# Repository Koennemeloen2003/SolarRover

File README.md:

Code en PSB design voor het Solar Rover project van hogeschool Zuyd

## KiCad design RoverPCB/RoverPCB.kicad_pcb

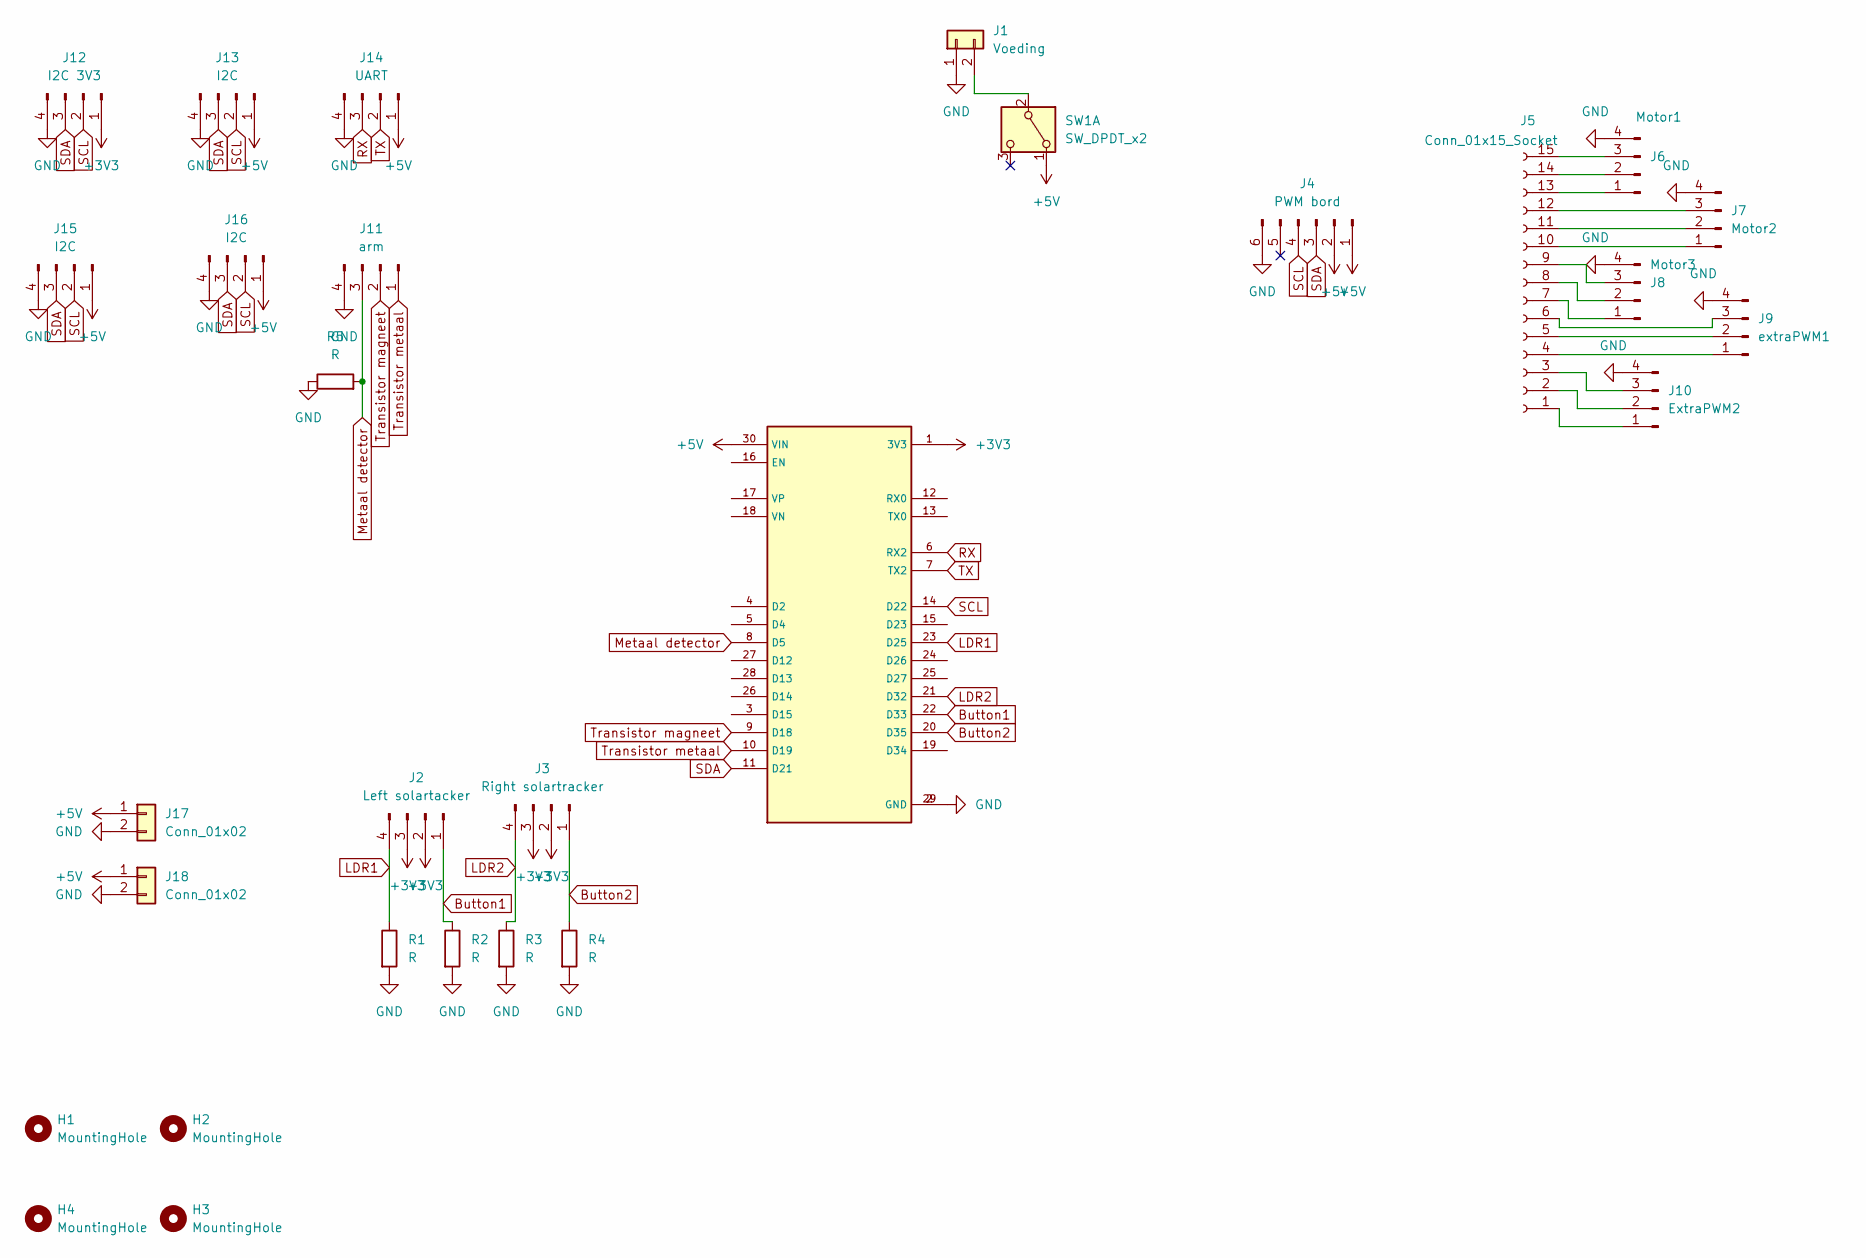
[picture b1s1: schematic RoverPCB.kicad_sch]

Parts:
H1, H2, H3, H4: MountingHole; MountingHole_3.2mm_M3
J1: Voeding; PhoenixContact_MSTBA_2,5_2-G-5,08_1x02_P5.08mm_Horizontal
J2: Left solartacker; Audio jack
J3: Right solartracker; Audio jack
J4: PWM bord; PinHeader_1x06_P2.54mm_Vertical
J5: Conn_01x15_Socket; PinHeader_1x15_P2.54mm_Vertical
J6: Motor1; Audio jack
J7: Motor2; Audio jack
J8: Motor3; Audio jack
J9: extraPWM1; Audio jack
J10: ExtraPWM2; Audio jack
J11: arm; Audio jack
J12: I2C 3V3; Audio jack
J13, J15, J16: I2C; Audio jack
J14: UART; Audio jack
J17, J18: Conn_01x02; PinHeader_1x02_P2.54mm_Vertical
R1, R2, R3, R4, R5: R; R_Axial_DIN0204_L3.6mm_D1.6mm_P7.62mm_Horizontal
SW1: SW_DPDT_x2; SW_CuK_SPDT_Angled
U1: ESP32_DEVKIT_V1_op_voetjes2rij

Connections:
+3V3: J2.2, J2.3, J3.2, J3.3, J12.1, U1.1 (3V3)
+5V: J4.1, J4.2, J13.1, J14.1, J15.1, J16.1, J17.1, J18.1, SW1.1 (A), U1.30 (VIN)
Button1: J2.1, R2.1, U1.22 (D33)
Button2: J3.1, R4.1, U1.20 (D35)
GND: J1.1, J4.6, J6.4, J7.4, J8.4, J9.4, J10.4, J11.4, J12.4, J13.4, J14.4, J15.4, J16.4, J17.2, J18.2, R1.2, R2.2, R3.2, R4.2, R5.1, U1.2 (GND), U1.29 (GND)
LDR1: J2.4, R1.1, U1.23 (D25)
LDR2: J3.4, R3.1, U1.21 (D32)
Metaal detector: J11.3, R5.2, U1.8 (D5)
unnamed: J1.2, SW1.2 (B)
unnamed: J5.4, J9.1
unnamed: J5.5, J9.2
unnamed: J5.6, J9.3
unnamed: J5.7, J8.1
unnamed: J5.8, J8.2
unnamed: J5.9, J8.3
unnamed: J5.10, J7.1
unnamed: J5.11, J7.2
unnamed: J5.12, J7.3
unnamed: J5.13, J6.1
unnamed: J5.14, J6.2
unnamed: J5.15, J6.3
unnamed: J5.1, J10.1
unnamed: J5.2, J10.2
unnamed: J5.3, J10.3
RX: J14.3, U1.6 (RX2)
SCL: J4.4, J12.2, J13.2, J15.2, J16.2, U1.14 (D22)
SDA: J4.3, J12.3, J13.3, J15.3, J16.3, U1.11 (D21)
TX: J14.2, U1.7 (TX2)
Transistor magneet: J11.2, U1.9 (D18)
Transistor metaal: J11.1, U1.10 (D19)

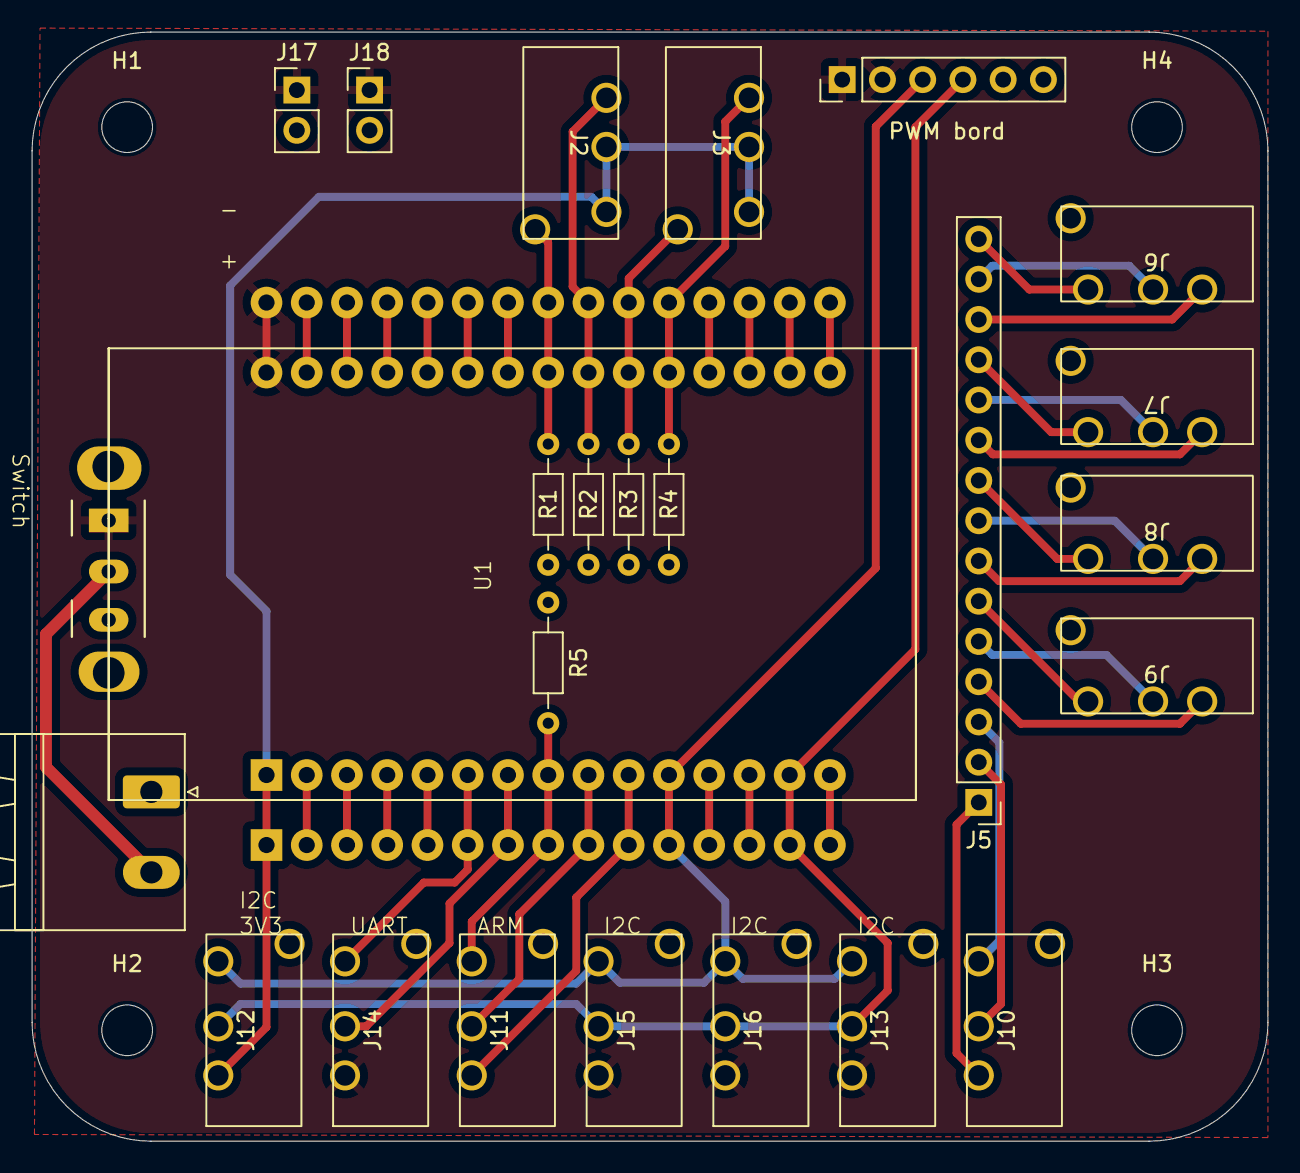
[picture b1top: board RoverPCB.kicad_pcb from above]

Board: 2 copper layers, 78.0 x 70.0 mm, 29 parts (0 on the bottom side), 30 nets.

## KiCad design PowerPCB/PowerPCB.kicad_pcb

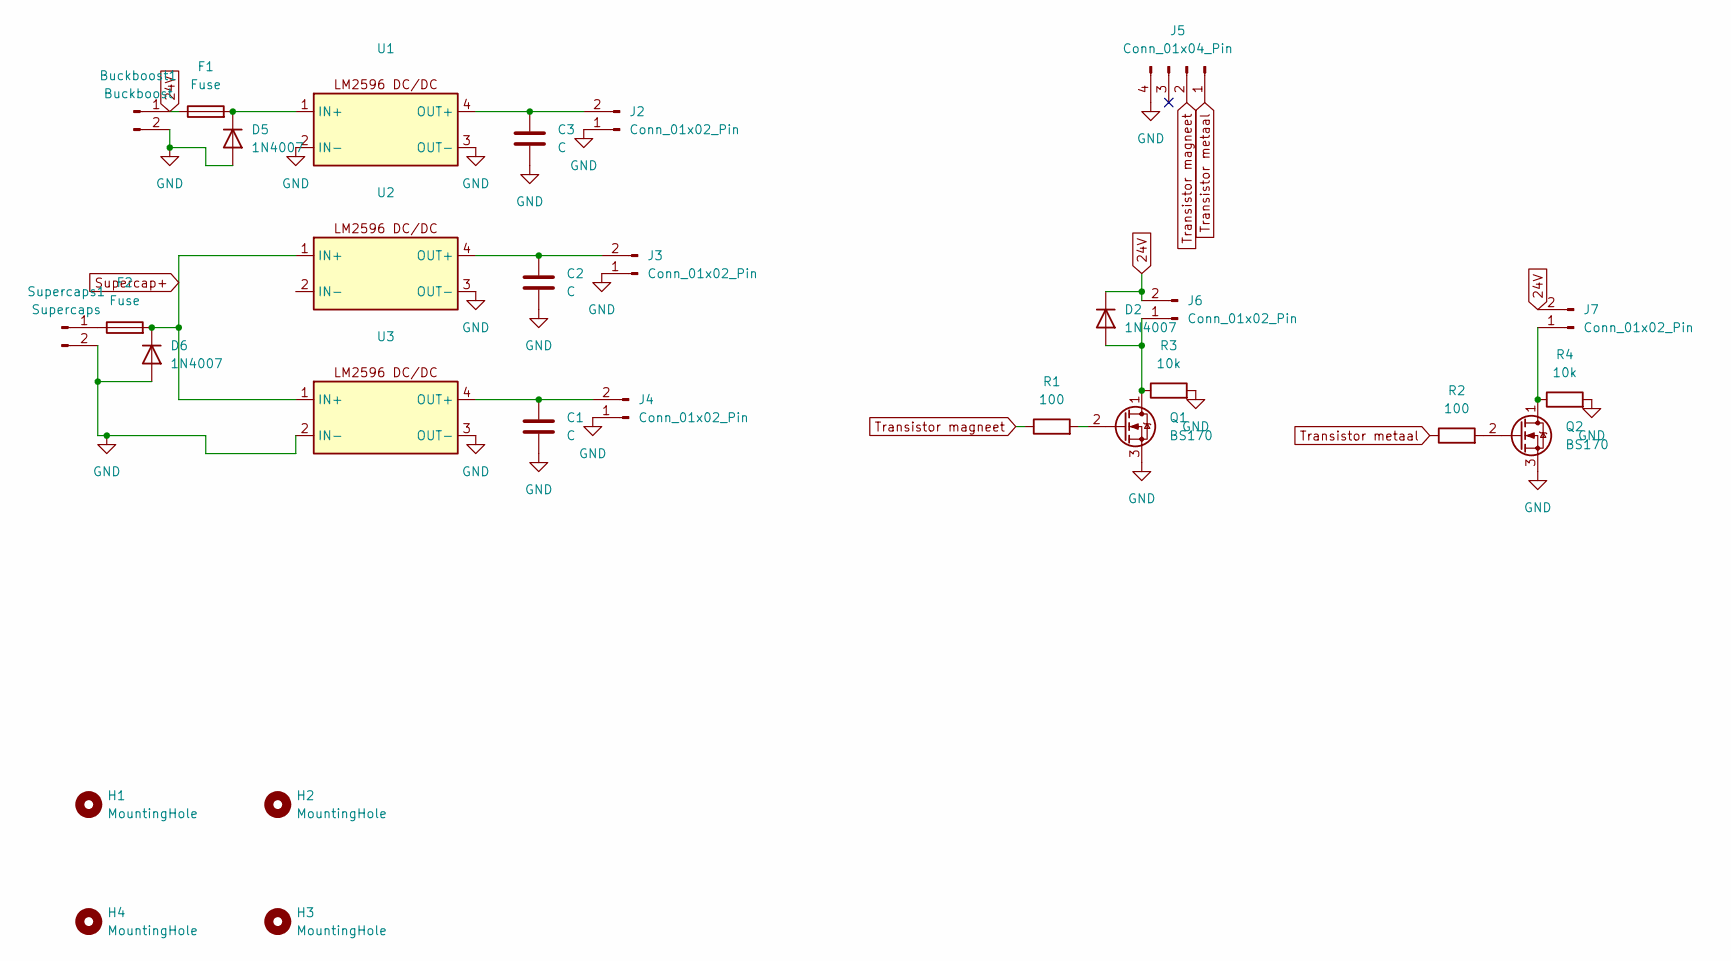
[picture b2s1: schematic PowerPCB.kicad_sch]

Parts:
Buckboost1: Buckboost; PhoenixContact_MSTBA_2,5_2-G-5,08_1x02_P5.08mm_Horizontal
C1, C2, C3: C; CP_Radial_D5.0mm_P2.50mm
D2, D5, D6: 1N4007; D_DO-41_SOD81_P10.16mm_Horizontal
F1, F2: Fuse; RB500-50
H1, H2, H3, H4: MountingHole; MountingHole_3.2mm_M3
J2, J3, J4, J6, J7: Conn_01x02_Pin; PhoenixContact_MSTBA_2,5_2-G-5,08_1x02_P5.08mm_Horizontal
J5: Conn_01x04_Pin; Audio jack
Q1, Q2: BS170; TO-92_Inline
R1, R2: 100; R_Axial_DIN0204_L3.6mm_D1.6mm_P7.62mm_Horizontal
R3, R4: 10k; R_Axial_DIN0204_L3.6mm_D1.6mm_P7.62mm_Horizontal
Supercaps1: Supercaps; PhoenixContact_MSTBA_2,5_2-G-5,08_1x02_P5.08mm_Horizontal
U1, U2, U3: LM2596_module_opvoetjes

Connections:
24V: Buckboost1.1, D2.1 (K), F1.1, J6.2, J7.2
GND: Buckboost1.2, C1.2, C2.2, C3.2, D5.2 (A), D6.2 (A), J2.1, J3.1, J4.1, J5.4, Q1.3 (S), Q2.3 (S), R3.2, R4.2, Supercaps1.2, U1.2 (IN-), U1.3 (OUT-), U2.3 (OUT-), U3.2 (IN-), U3.3 (OUT-)
unnamed: D2.2 (A), J6.1, Q1.1 (D), R3.1
unnamed: D5.1 (K), F1.2, U1.1 (IN+)
unnamed: C3.1, J2.2, U1.4 (OUT+)
unnamed: C2.1, J3.2, U2.4 (OUT+)
unnamed: C1.1, J4.2, U3.4 (OUT+)
unnamed: J7.1, Q2.1 (D), R4.1
unnamed: Q1.2 (G), R1.2
unnamed: Q2.2 (G), R2.2
unnamed: F2.1, Supercaps1.1
Supercap+: D6.1 (K), F2.2, U2.1 (IN+), U3.1 (IN+)
Transistor magneet: J5.2, R1.1
Transistor metaal: J5.1, R2.1

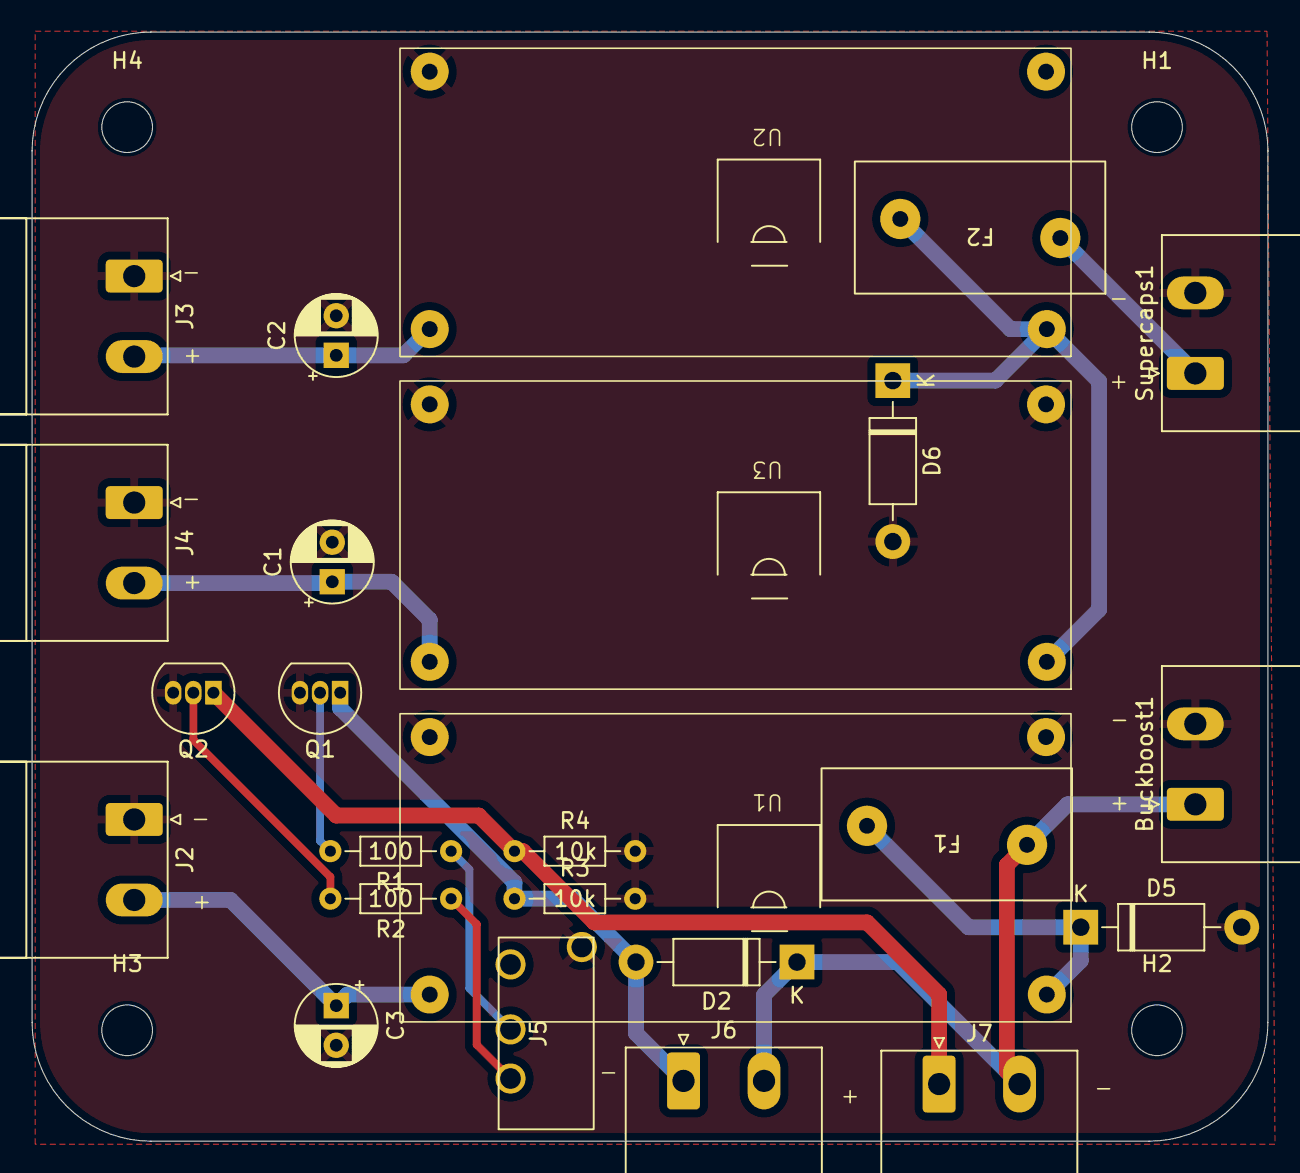
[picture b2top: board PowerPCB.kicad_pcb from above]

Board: 2 copper layers, 78.0 x 70.0 mm, 29 parts (0 on the bottom side), 14 nets.

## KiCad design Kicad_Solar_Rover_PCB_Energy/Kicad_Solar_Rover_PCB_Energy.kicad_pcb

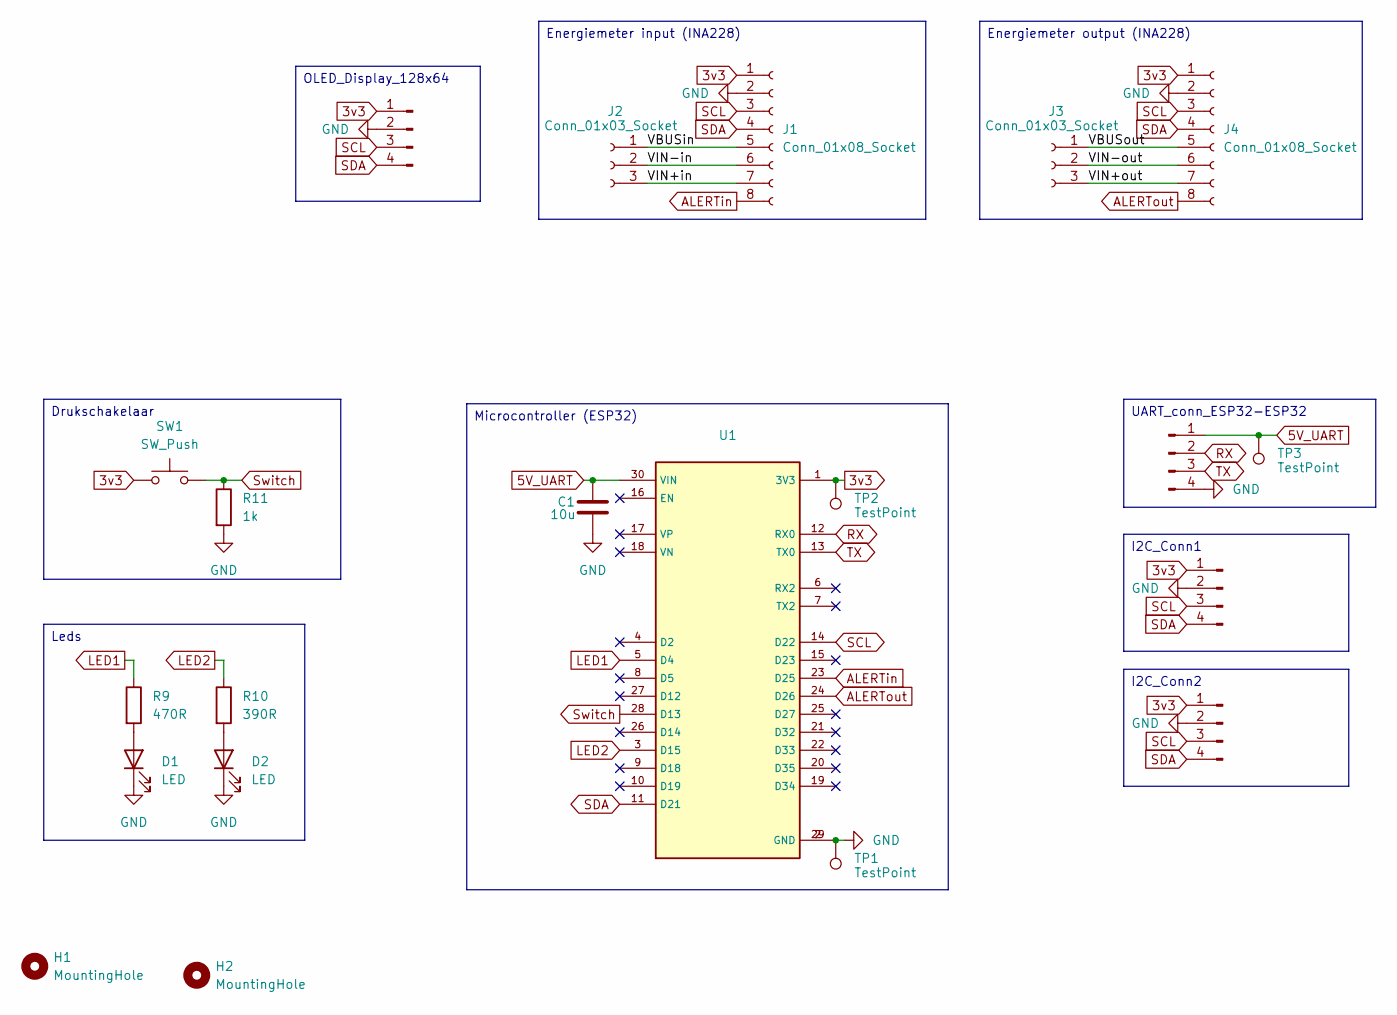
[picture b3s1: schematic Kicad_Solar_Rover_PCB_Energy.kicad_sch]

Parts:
C1: 10u; CP_Axial_L10.0mm_D4.5mm_P15.00mm_Horizontal
D1, D2: LED; LED_D5.0mm; MPN LWTTM1P1FK0PN005
H1, H2: MountingHole; MountingHole_4.3mm_M4
J1, J4: Conn_01x08_Socket; PinSocket_1x08_P2.54mm_Vertical
J2, J3: Conn_01x03_Socket; PhoenixContact_MSTBA_2,5_3-G-5,08_1x03_P5.08mm_Horizontal
J5, J7, J8, J9: Conn_01x04_Pin; Audio jack; MPN 9-103329-0
R9: 470R; R_Axial_DIN0207_L6.3mm_D2.5mm_P7.62mm_Horizontal; MPN CRCW0603-1.3K-E3
R10: 390R; R_Axial_DIN0207_L6.3mm_D2.5mm_P7.62mm_Horizontal; MPN CRCW0603-1.3K-E3
R11: 1k; R_Axial_DIN0207_L6.3mm_D2.5mm_P7.62mm_Horizontal; MPN CRCW06031K00FKEI
SW1: SW_Push; SW_PUSH_6mm_H8mm; MPN KMR231GLFS
TP1, TP2, TP3: TestPoint; TestPoint_Pad_D1.0mm
U1: ESP32_DEVKIT_V1

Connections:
3v3: J1.1, J4.1, J7.1, J8.1, J9.1, SW1.1, TP2.1, U1.1 (3V3)
5V_UART: C1.1, J5.1, TP3.1, U1.30 (VIN)
/VBUSin: J1.5, J2.1
/VBUSout: J3.1, J4.5
/VIN+in: J1.7, J2.3
/VIN+out: J3.3, J4.7
/VIN-in: J1.6, J2.2
/VIN-out: J3.2, J4.6
ALERTin: J1.8, U1.23 (D25)
ALERTout: J4.8, U1.24 (D26)
GND: C1.2, D1.1 (K), D2.1 (K), J1.2, J4.2, J5.4, J7.2, J8.2, J9.2, R11.2, TP1.1, U1.2 (GND), U1.29 (GND)
LED1: R9.1, U1.5 (D4)
LED2: R10.1, U1.3 (D15)
unnamed: D1.2 (A), R9.2
unnamed: D2.2 (A), R10.2
RX: J5.2, U1.12 (RX0)
SCL: J1.3, J4.3, J7.3, J8.3, J9.3, U1.14 (D22)
SDA: J1.4, J4.4, J7.4, J8.4, J9.4, U1.11 (D21)
Switch: R11.1, SW1.2, U1.28 (D13)
TX: J5.3, U1.13 (TX0)

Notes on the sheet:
I2C_Conn1
Leds
Microcontroller (ESP32)
Energiemeter input (INA228)
I2C_Conn2
UART_conn_ESP32-ESP32
OLED_Display_128x64
Drukschakelaar
Energiemeter output (INA228)

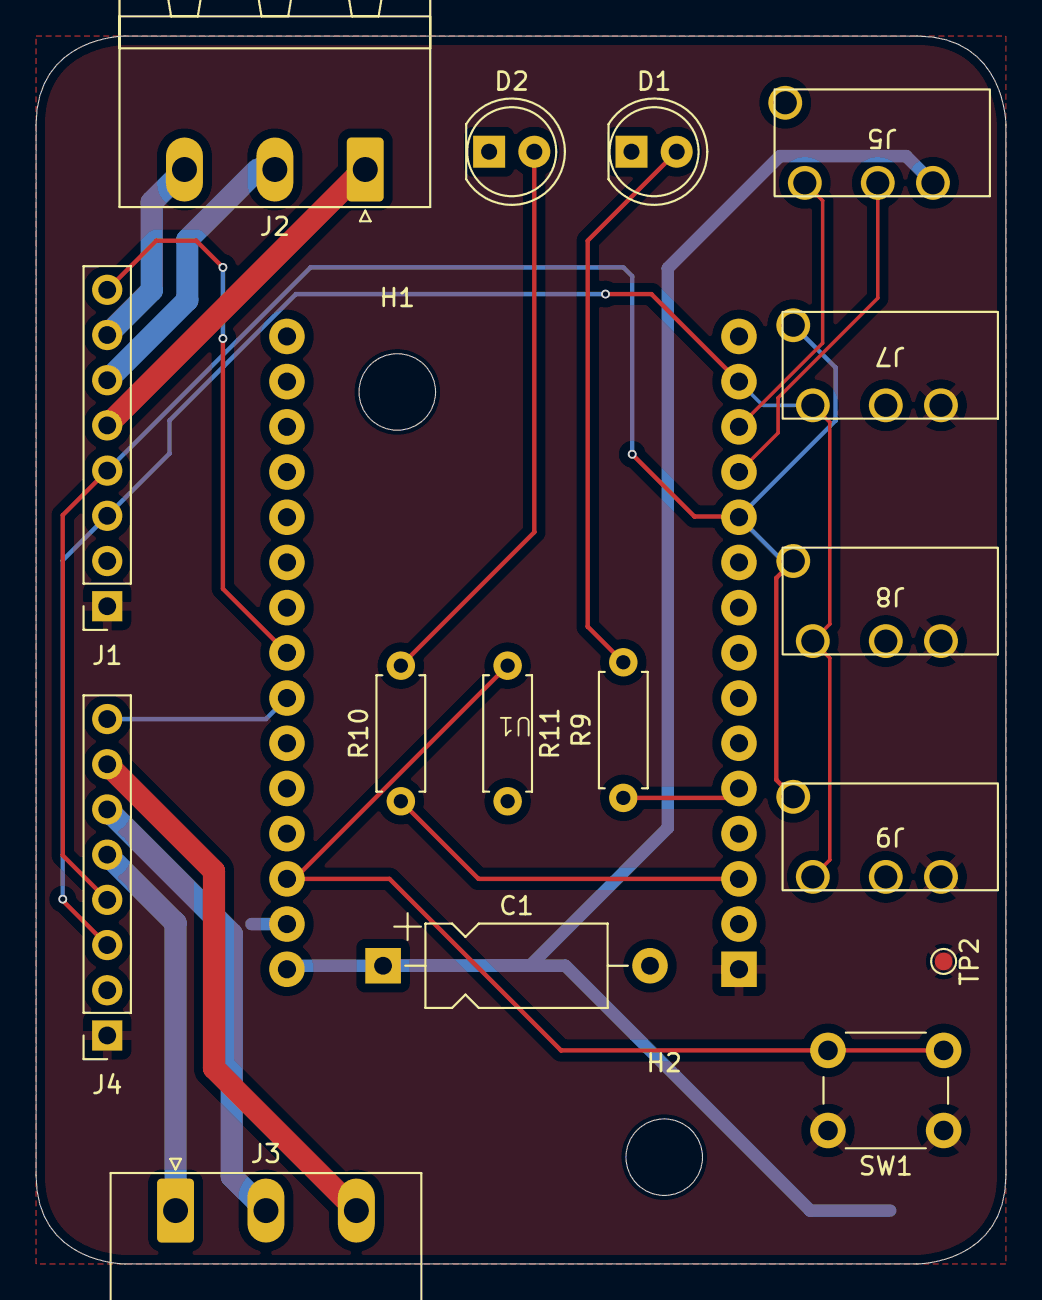
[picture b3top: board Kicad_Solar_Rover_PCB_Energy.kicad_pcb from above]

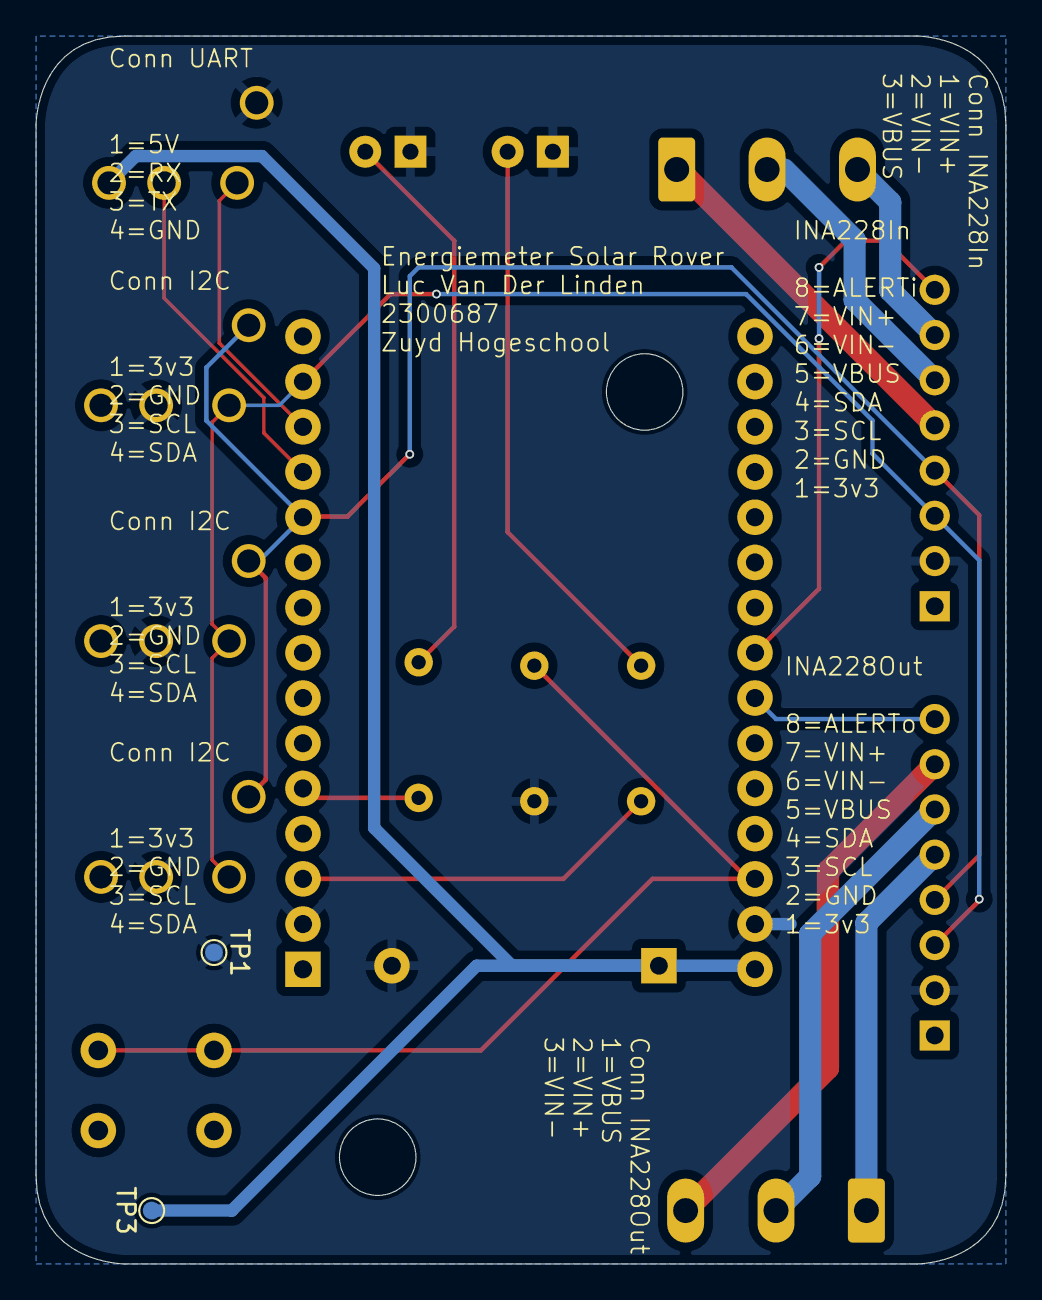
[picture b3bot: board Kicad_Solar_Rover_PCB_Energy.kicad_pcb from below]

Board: 2 copper layers, 54.5 x 69.0 mm, 21 parts (2 on the bottom side), 20 nets.

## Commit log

2025-03-24 Huidige code geupload
2025-03-24 Linetracker initial commit
2025-03-24 line tracker + solar tracker motor
    line tracker kan in en uitgeschakeld worden met de up knop op de Dpad en de solar tracker motor kan een stap bewegen door een druk op de down knop
2025-03-25 optimalisatie
2025-04-02 tracker motor kan nu ook achteruit
2025-04-10 heel veel dingen
2025-04-10 kleine veranderingen
2025-04-10 iets
2025-04-11 final?
2025-04-14 Finak final?
2025-04-14 oprecht de laatste
2025-04-15 oprecht 100% zeker de laatste
2025-05-07 PCB design voor rover
2025-05-07 pcb updates
2025-05-19 PCBs
2025-05-19 PCBRover final
2025-05-20 PowerPCB
2025-05-20 test
2025-05-20 test2
2025-06-24 2 esps
2025-06-26 wifi beter
2025-06-29 buttons aangepast
2025-06-29 tekeing rover
2025-07-01 final
